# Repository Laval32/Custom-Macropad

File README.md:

# Custom Macropad

A custom 3×3 macropad built from scratch with a **XIAO RP2040**, custom PCB, and 3D-printed case.

## Features

* 9 programmable keys
* EC11 rotary encoder with push button
* 0.91" OLED display
* Custom PCB designed in KiCad
* 3D-printed two-piece case
* QMK firmware
* DSA keycaps

## Design

### Schematic

### PCB

### Case

## BOM

| Quantity | Part                               |
| -------- | ---------------------------------- |
| 1        | XIAO RP2040                        |
| 9        | 1N4148 Diodes                      |
| 9        | Cherry MX Switches                 |
| 1        | EC11E Rotary Encoder (with switch) |
| 1        | 0.91" OLED Display                 |
| 9        | DSA Keycaps                        |
| 4        | M3×16mm Screws                     |
| 4        | M3×5mm×4mm Heatset Inserts         |
| 1        | 3D-Printed Case (Top + Bottom)     |

## Firmware

The macropad uses **QMK** for key mapping and rotary encoder functionality.

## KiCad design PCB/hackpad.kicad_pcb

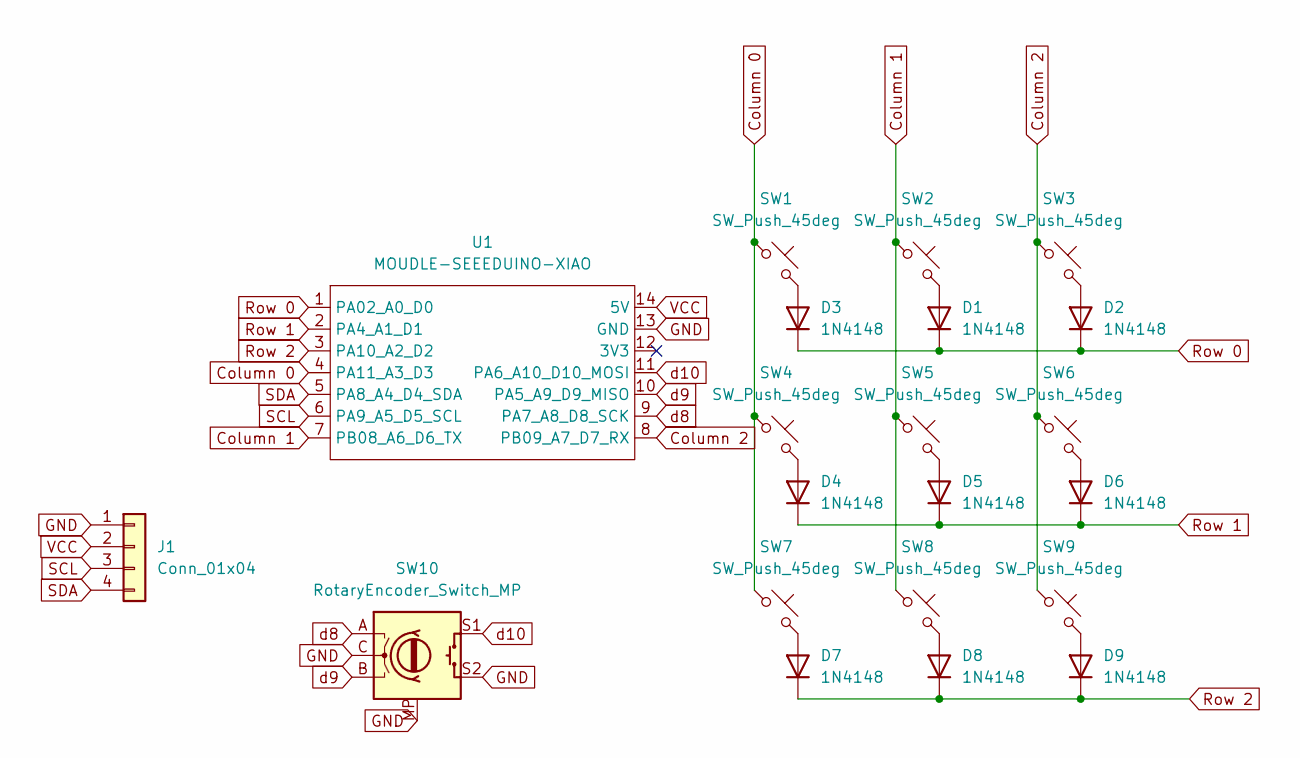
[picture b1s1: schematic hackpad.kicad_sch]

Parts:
D1, D2, D3, D4, D5, D6, D7, D8, D9: 1N4148; D_DO-35_SOD27_P7.62mm_Horizontal
J1: Conn_01x04; SSD1306-0.91-OLED-4pin-128x32
SW1, SW2, SW3, SW4, SW5, SW6, SW7, SW8, SW9: SW_Push_45deg; SW_Cherry_MX_1.00u_PCB
SW10: RotaryEncoder_Switch_MP; RotaryEncoder_Alps_EC11E-Switch_Vertical_H20mm
U1: MOUDLE-SEEEDUINO-XIAO; XIAO-Generic-Hybrid-14P-2.54-21X17.8MM

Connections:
Column 0: SW1.1, SW4.1, SW7.1, U1.4 (PA11_A3_D3)
Column 1: SW2.1, SW5.1, SW8.1, U1.7 (PB08_A6_D6_TX)
Column 2: SW3.1, SW6.1, SW9.1, U1.8 (PB09_A7_D7_RX)
GND: J1.1, SW10.C, SW10.MP, SW10.S2, U1.13 (GND)
unnamed: D1.2 (A), SW2.2
unnamed: D2.2 (A), SW3.2
unnamed: D3.2 (A), SW1.2
unnamed: D4.2 (A), SW4.2
unnamed: D5.2 (A), SW5.2
unnamed: D6.2 (A), SW6.2
unnamed: D7.2 (A), SW7.2
unnamed: D8.2 (A), SW8.2
unnamed: D9.2 (A), SW9.2
Row 0: D1.1 (K), D2.1 (K), D3.1 (K), U1.1 (PA02_A0_D0)
Row 1: D4.1 (K), D5.1 (K), D6.1 (K), U1.2 (PA4_A1_D1)
Row 2: D7.1 (K), D8.1 (K), D9.1 (K), U1.3 (PA10_A2_D2)
SCL: J1.3, U1.6 (PA9_A5_D5_SCL)
SDA: J1.4, U1.5 (PA8_A4_D4_SDA)
VCC: J1.2, U1.14 (5V)
d8: SW10.A, U1.9 (PA7_A8_D8_SCK)
d9: SW10.B, U1.10 (PA5_A9_D9_MISO)
d10: SW10.S1, U1.11 (PA6_A10_D10_MOSI)

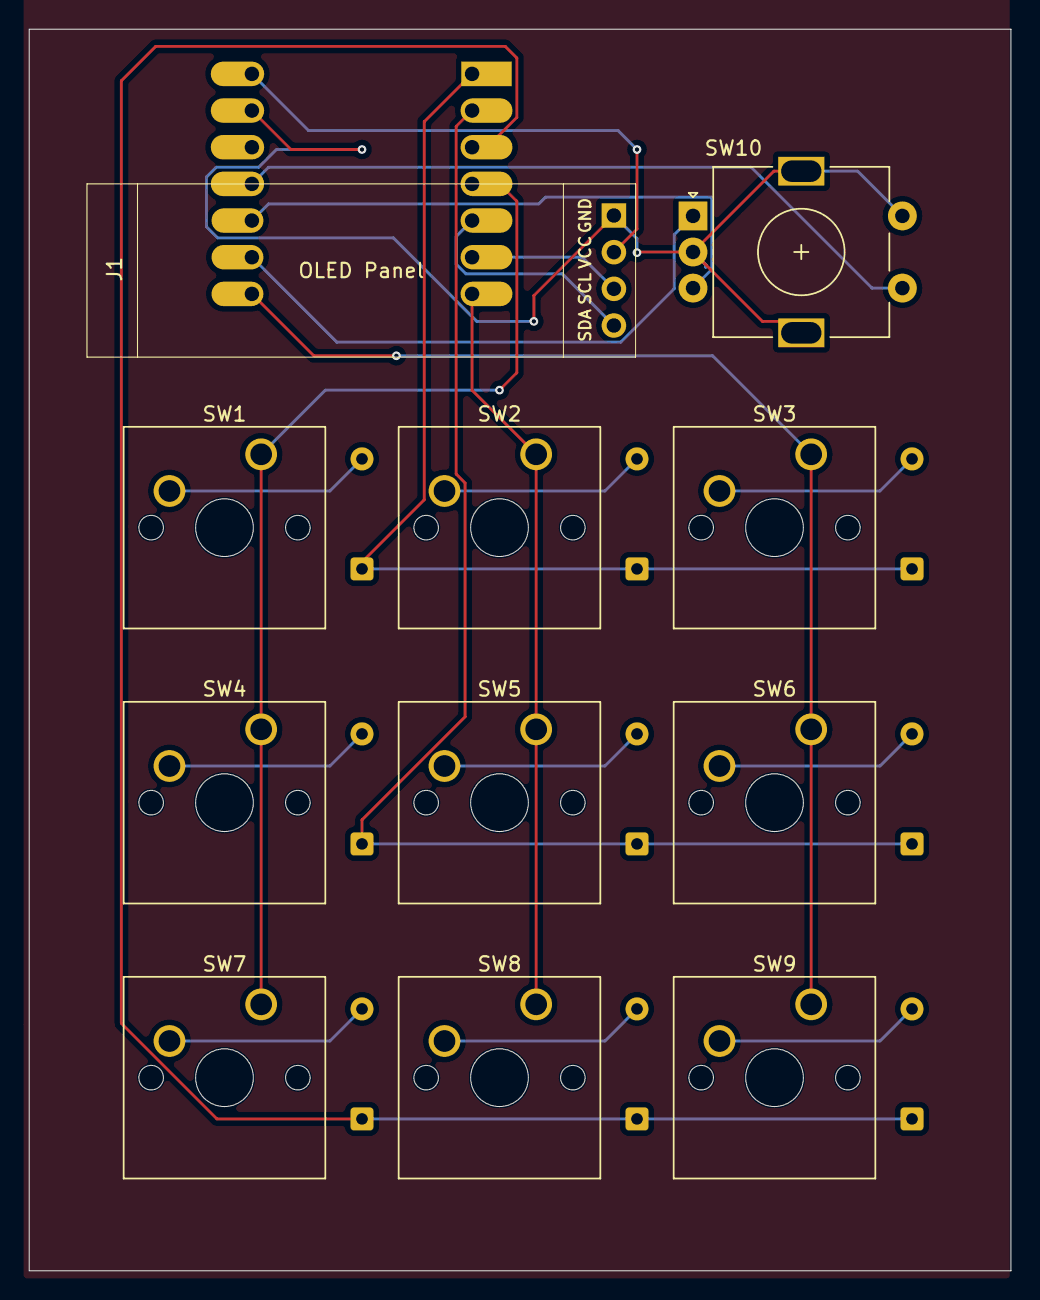
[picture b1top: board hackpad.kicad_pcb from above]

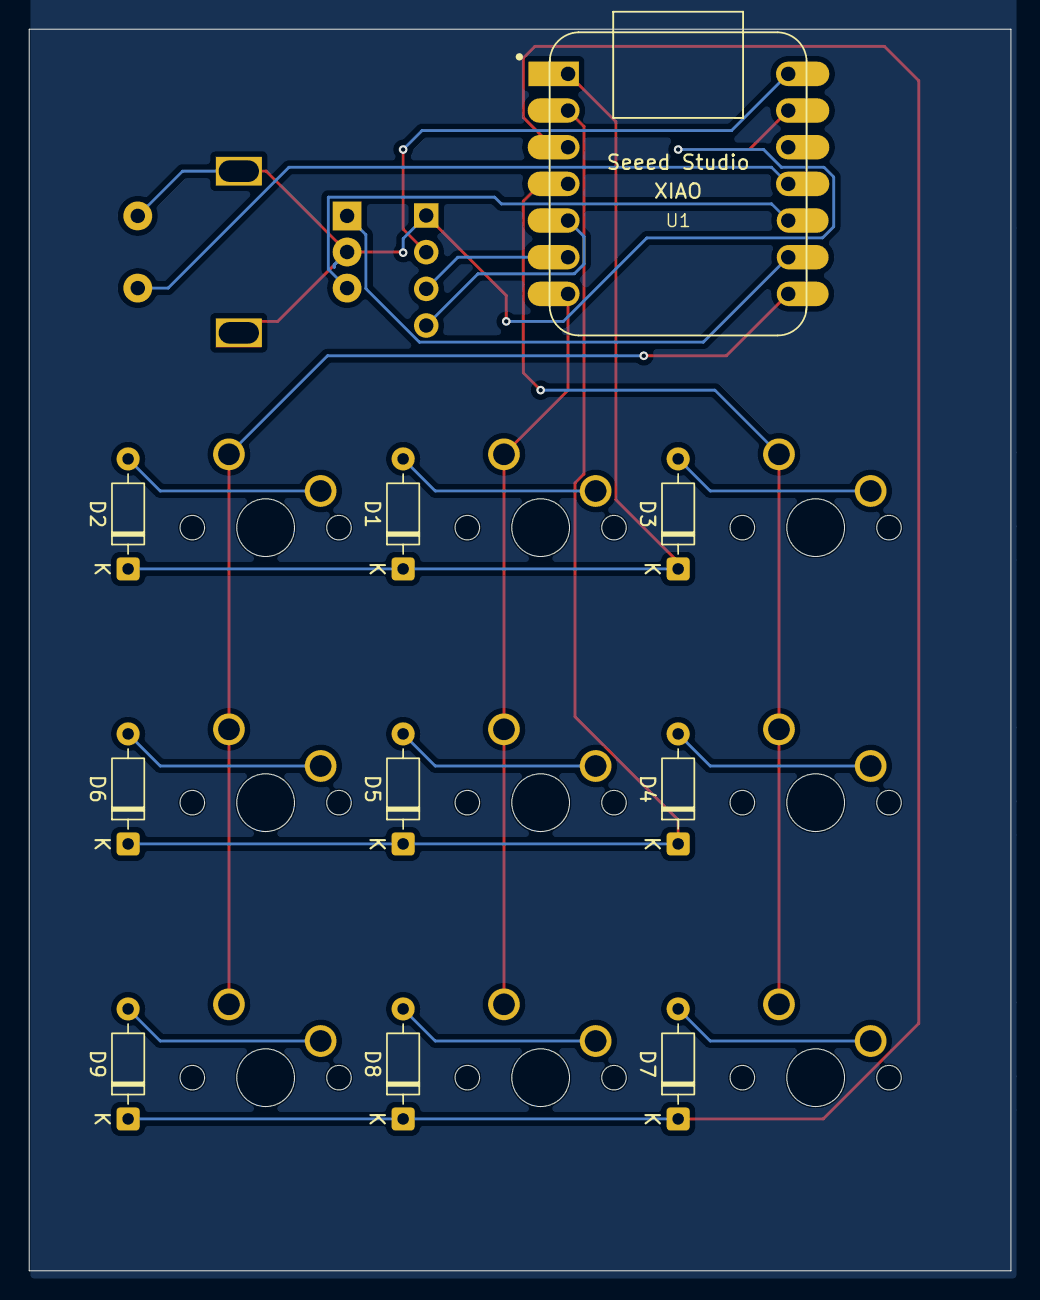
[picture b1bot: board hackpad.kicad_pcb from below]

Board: 2 copper layers, 68.0 x 86.0 mm, 21 parts (10 on the bottom side), 22 nets.
